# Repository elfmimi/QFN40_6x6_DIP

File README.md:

# QFN40 6x6mm to Slim DIP adapter
This is an adapter PCB to mount SMD components in 6x6mm QFN40 package on a breadboard.

Caution: row-to-row = 500 mil

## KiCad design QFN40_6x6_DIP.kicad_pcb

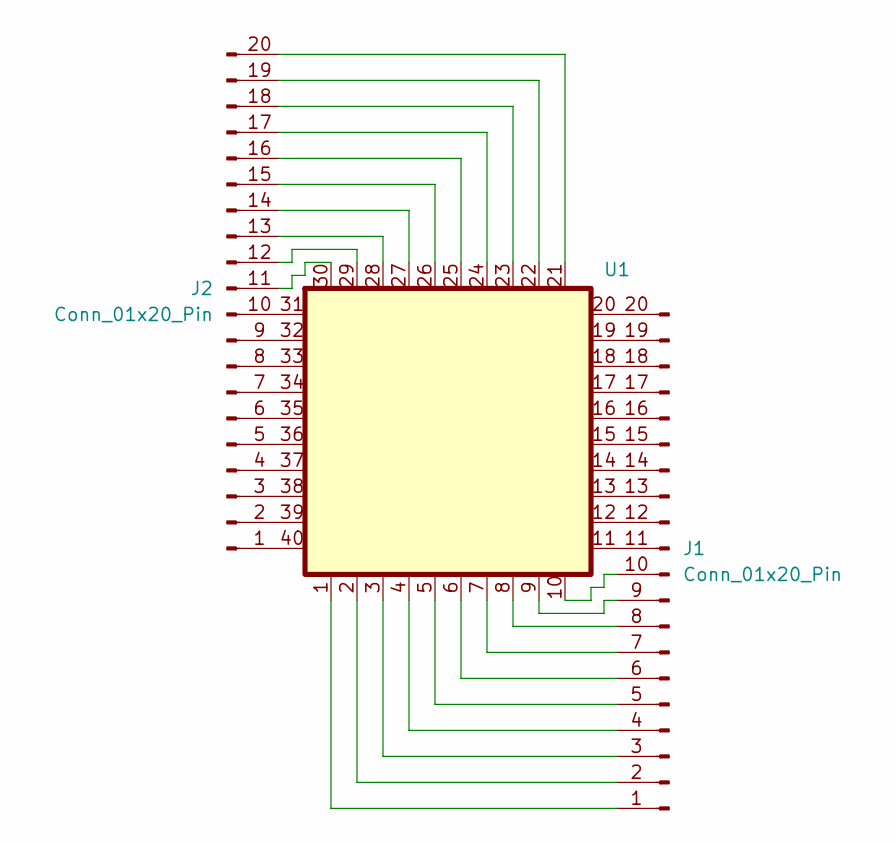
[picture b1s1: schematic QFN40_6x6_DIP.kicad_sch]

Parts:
J1, J2: Conn_01x20_Pin; PinHeader_1x20_P2.54mm_Vertical
U1: QFN-40-1EP_6x6mm_P0.5mm_EP4.6x4.6mm

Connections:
unnamed: J1.1, U1.1
unnamed: J1.2, U1.2
unnamed: J1.3, U1.3
unnamed: J1.4, U1.4
unnamed: J1.5, U1.5
unnamed: J1.6, U1.6
unnamed: J1.7, U1.7
unnamed: J1.8, U1.8
unnamed: J1.9, U1.9
unnamed: J1.10, U1.10
unnamed: J1.11, U1.11
unnamed: J1.12, U1.12
unnamed: J1.13, U1.13
unnamed: J1.14, U1.14
unnamed: J1.15, U1.15
unnamed: J1.16, U1.16
unnamed: J1.17, U1.17
unnamed: J1.18, U1.18
unnamed: J1.19, U1.19
unnamed: J1.20, U1.20
unnamed: J2.1, U1.40
unnamed: J2.2, U1.39
unnamed: J2.3, U1.38
unnamed: J2.4, U1.37
unnamed: J2.5, U1.36
unnamed: J2.6, U1.35
unnamed: J2.7, U1.34
unnamed: J2.8, U1.33
unnamed: J2.9, U1.32
unnamed: J2.10, U1.31
unnamed: J2.11, U1.30
unnamed: J2.12, U1.29
unnamed: J2.13, U1.28
unnamed: J2.14, U1.27
unnamed: J2.15, U1.26
unnamed: J2.16, U1.25
unnamed: J2.17, U1.24
unnamed: J2.18, U1.23
unnamed: J2.19, U1.22
unnamed: J2.20, U1.21

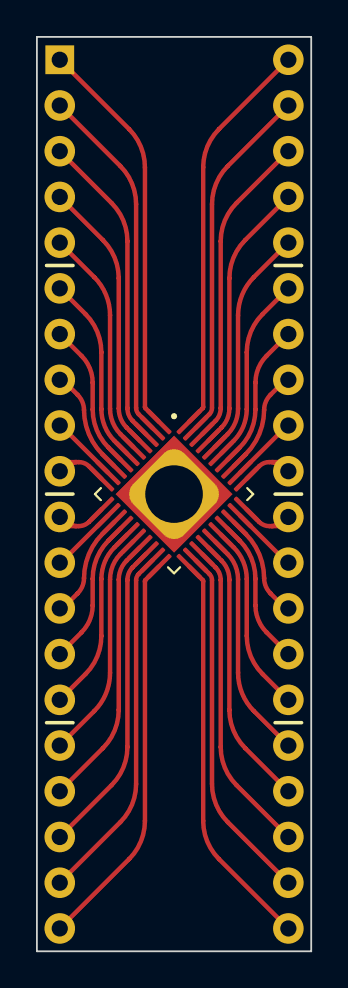
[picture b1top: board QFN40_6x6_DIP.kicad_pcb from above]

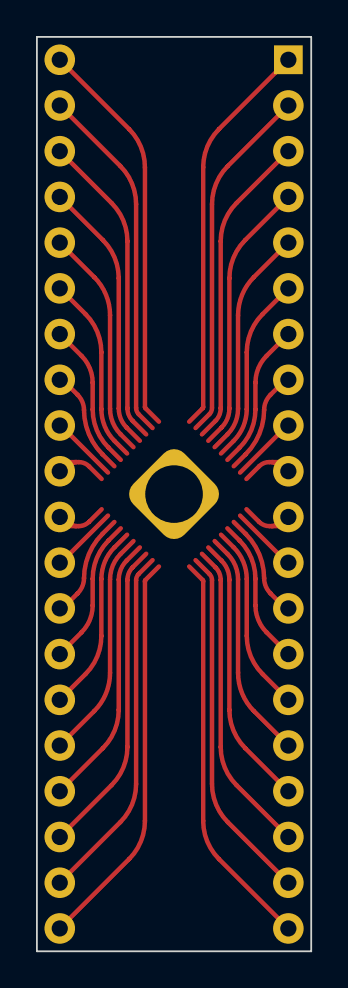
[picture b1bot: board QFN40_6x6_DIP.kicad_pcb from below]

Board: 2 copper layers, 15.2 x 50.8 mm, 3 parts (2 on the bottom side), 40 nets.
